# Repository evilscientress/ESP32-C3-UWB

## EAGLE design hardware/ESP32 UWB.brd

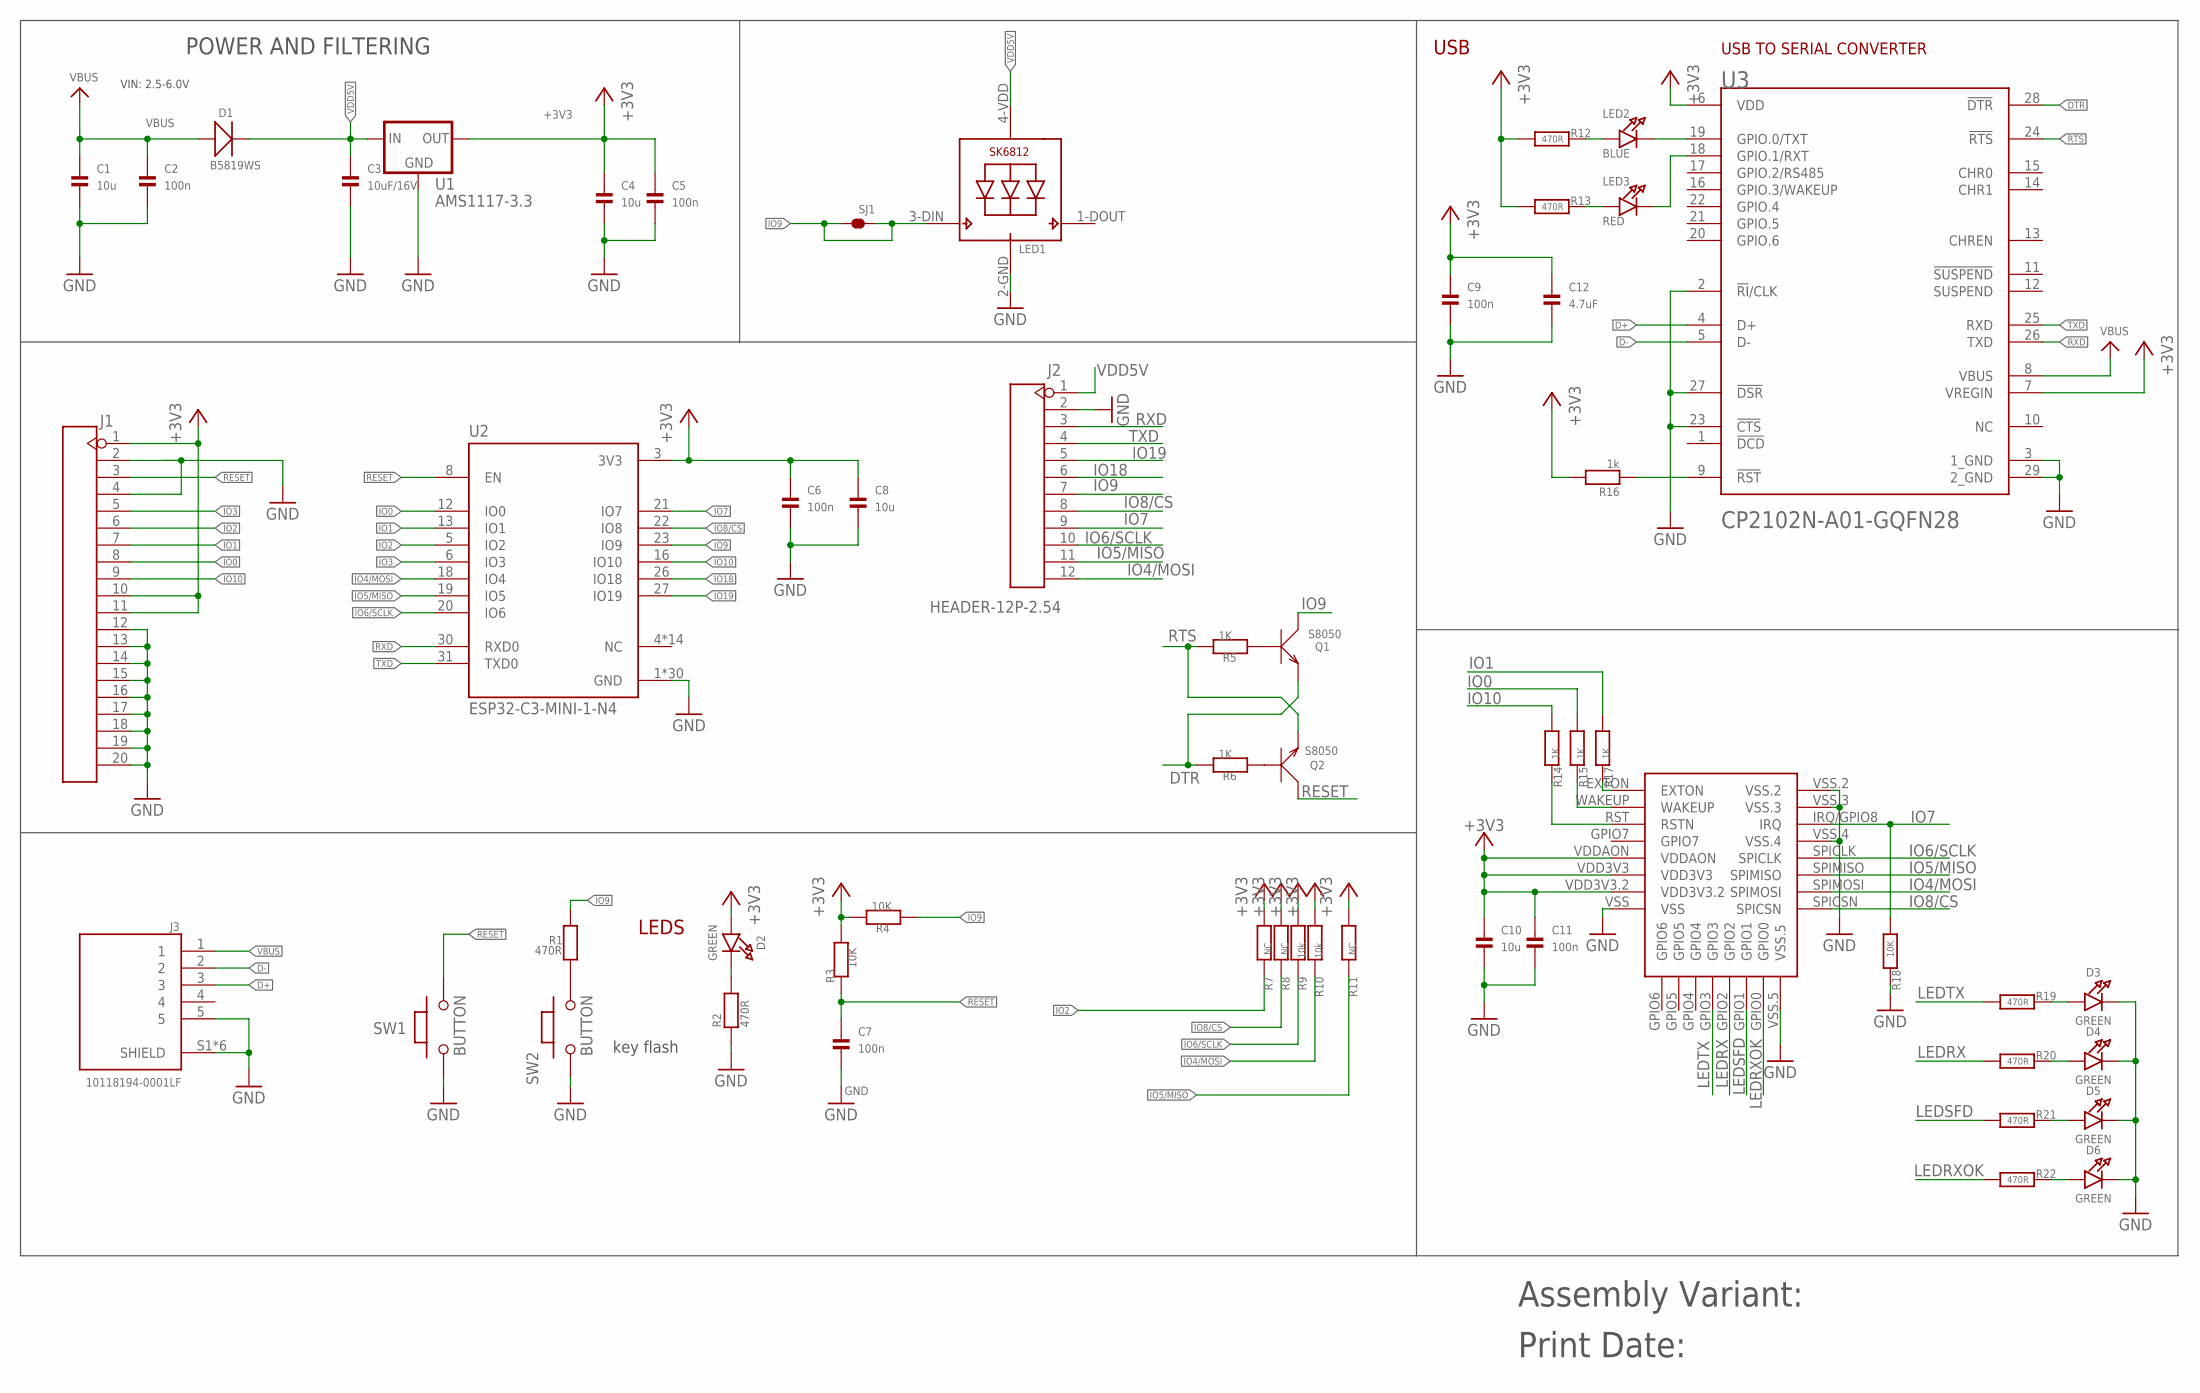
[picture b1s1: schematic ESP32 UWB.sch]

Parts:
C1, C4, C8, C10: 10u; 0603
C2, C5, C6, C7, C9, C11: 100n; 0603
C3: 10uF/16V; 0603
C12: 4.7uF; 0603
D1: B5819WS; SOD323
D2, D3, D4, D5, D6: GREEN; CHIPLED_0805_NOOUTLINE
J1: HEADER-20P-2.54; 20P-2.54
J2: HEADER-12P-2.54; 12P-2.54
J3: 10118194-0001LF; AMPHENOL_10118194-0001LF
LED1: SK6812_3535; LED3535
LED2: BLUE; CHIPLED_0603_NOOUTLINE
LED3: RED; CHIPLED_0603_NOOUTLINE
Q1, Q2: S8050; SOT23
R1, R2, R12, R13, R19, R20, R21, R22: 470R; 0603
R3, R4, R18: 10K; 0603
R5, R6, R14, R15, R17: 1K; 0603
R7, R8, R11: NC; 0603
R9, R10: 10k; 0603
R16: 1k; 0603
SJ1: SJS; SJ_S
SW1, SW2: BUTTON; 157SW
U1: AMS1117-3.3; SOT223
U2: ESP32-C3-MINI-1-N4; XCVR_ESP32-C3-MINI-1-N4
U3: SILICON_LABS_CP2102N-A01-GQFN28SILICON_LABS_CP210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; SILICON_LABS_CP2102N-A01-GQFN28_3
U4: DWM1000

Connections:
+3V3: C4.1, C5.1, C6.1, C8.1, C9.1, C10.1, C11.1, C12.1, D2.A, J1.1, J1.10, J1.11, R3.2, R4.2, R7.1, R8.1, R9.1, R10.1, R11.1, R12.1, R13.1, R16.2, U1.3 (OUT), U2.3 (3V3), U3.6 (VDD), U3.7 (VREGIN), U4.VDD3V3, U4.VDD3V3.2, U4.VDDAON
D+: J3.3, U3.4 (D+)
D-: J3.2, U3.5 (D-)
DTR: Q1.2 (E), R6.2, U3.28 (!DTR!)
GND: C1.2, C2.2, C3.2, C4.2, C5.2, C6.2, C7.2, C8.2, C9.2, C10.2, C11.2, C12.2, D3.C, D4.C, D5.C, D6.C, J1.2, J1.4, J1.12, J1.13, J1.14, J1.15, J1.16, J1.17, J1.18, J1.19, J1.20, J2.2, J3.5, J3.S1 (SHIELD), J3.S2 (SHIELD), J3.S3 (SHIELD), J3.S4 (SHIELD), J3.S5 (SHIELD), J3.S6 (SHIELD), LED1.2-GND (GND), R2.1, R18.2, SW1.1, SW2.1, U1.2 (GND), U2.1 (GND), U2.2 (GND), U2.11 (GND), U2.14 (GND), U2.36 (GND), U2.37 (GND), U2.38 (GND), U2.39 (GND), U2.40 (GND), U2.41 (GND), U2.42 (GND), U2.43 (GND), U2.44 (GND), U2.45 (GND), U2.46 (GND), U2.47 (GND), U2.48 (GND), U2.49_1 (GND), U2.49_2 (GND), U2.49_3 (GND), U2.49_4 (GND), U2.49_5 (GND), U2.49_6 (GND), U2.49_7 (GND), U2.49_8 (GND), U2.49_9 (GND), U2.50 (GND), U2.51 (GND), U2.52 (GND), U2.53 (GND), U3.2 (!RI!/CLK), U3.3 (1_GND), U3.23 (!CTS!), U3.27 (!DSR!), U3.29 (2_GND), U4.VSS, U4.VSS.2, U4.VSS.3, U4.VSS.4, U4.VSS.5
IO0: J1.8, R15.1, U2.12 (IO0)
IO1: J1.7, R17.1, U2.13 (IO1)
IO2: J1.6, R7.2, U2.5 (IO2)
IO3: J1.5, U2.6 (IO3)
IO4/MOSI: J2.12, R10.2, U2.18 (IO4), U4.SPIMOSI
IO5/MISO: J2.11, R11.2, U2.19 (IO5), U4.SPIMISO
IO6/SCLK: J2.10, R9.2, U2.20 (IO6), U4.SPICLK
IO7: J2.9, R18.1, U2.21 (IO7), U4.IRQ/GPIO8 (IRQ)
IO8/CS: J2.8, R8.2, U2.22 (IO8), U4.SPICSN
IO9: J2.7, LED1.3-DIN (DI), Q1.3 (C), R1.2, R4.1, SJ1.1, SJ1.2, U2.23 (IO9)
IO10: J1.9, R14.1, U2.16 (IO10)
IO18: J2.6, U2.26 (IO18)
IO19: J2.5, U2.27 (IO19)
LEDRX: R20.1, U4.GPIO2
LEDRXOK: R22.1, U4.GPIO0
LEDSFD: R21.1, U4.GPIO1
LEDTX: R19.1, U4.GPIO3
unnamed: D3.A, R19.2
unnamed: LED2.A, R12.2
unnamed: LED2.C, U3.19 (GPIO.0/TXT)
unnamed: LED3.A, R13.2
unnamed: D2.C, R2.2
unnamed: LED3.C, U3.18 (GPIO.1/RXT)
unnamed: R16.1, U3.9 (!RST!)
unnamed: R17.2, U4.EXTON
unnamed: R15.2, U4.WAKEUP
unnamed: R14.2, U4.RST (RSTN)
unnamed: Q2.1 (B), R6.1
unnamed: Q1.1 (B), R5.1
unnamed: R1.1, SW2.2
unnamed: D4.A, R20.2
unnamed: D5.A, R21.2
unnamed: D6.A, R22.2
RESET: C7.1, J1.3, Q2.3 (C), R3.1, SW1.2, U2.8 (EN)
RTS: Q2.2 (E), R5.2, U3.24 (!RTS!)
RXD: J2.3, U2.30 (RXD0), U3.26 (TXD)
TXD: J2.4, U2.31 (TXD0), U3.25 (RXD)
VBUS: C1.1, C2.1, D1.+, J3.1, U3.8 (VBUS)
VDD5V: C3.1, D1.-, J2.1, LED1.4-VDD (VDD), U1.1 (IN)

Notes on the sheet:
USB
LEDS
USB TO SERIAL CONVERTER
key flash
POWER AND FILTERING
VIN: 2.5-6.0V
Assembly Variant:
Print Date:

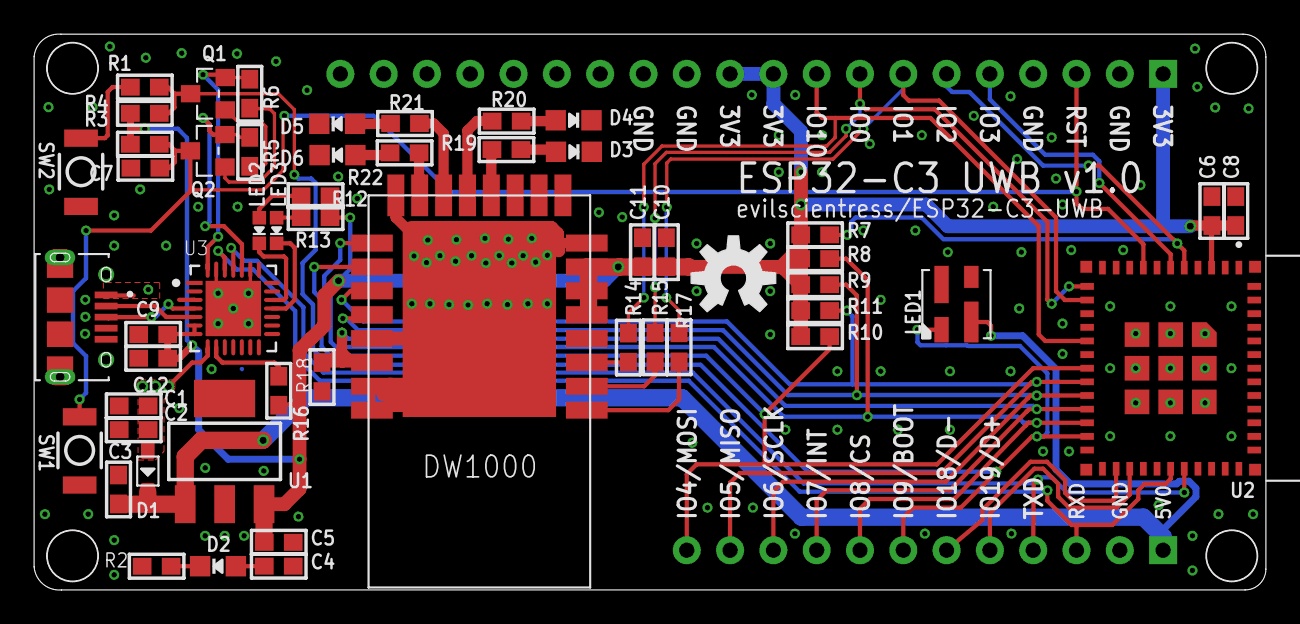
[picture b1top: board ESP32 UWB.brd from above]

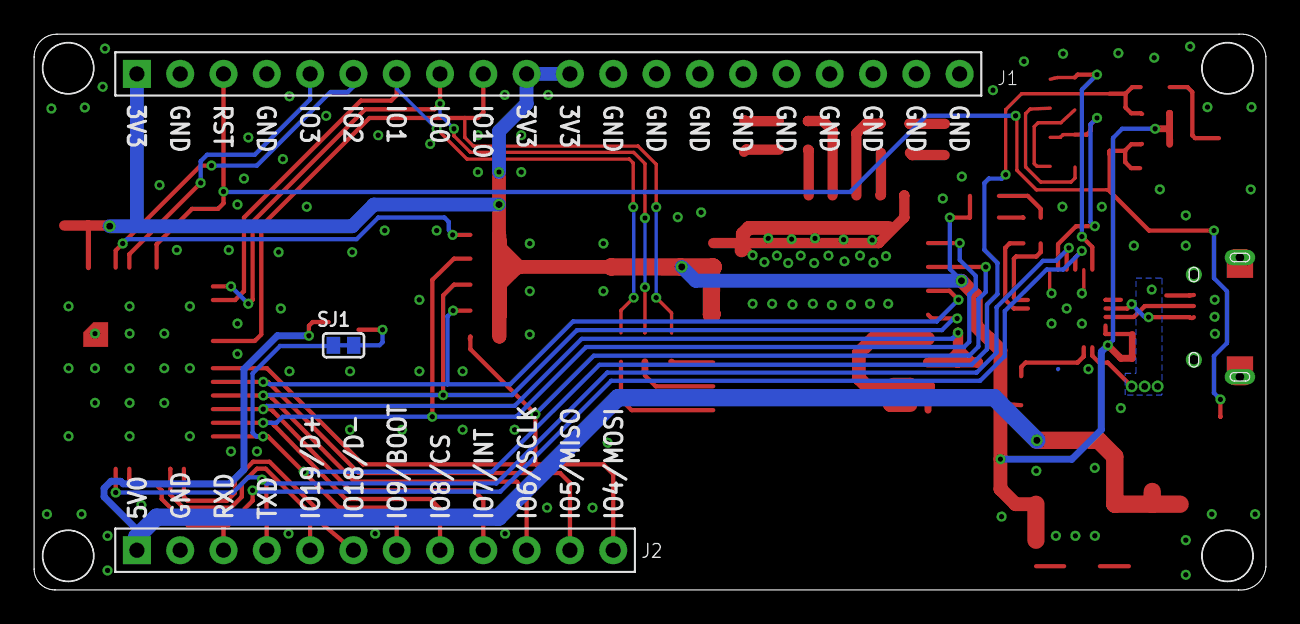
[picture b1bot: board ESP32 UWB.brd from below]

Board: 2 copper layers, 72.3 x 32.6 mm, 56 parts (3 on the bottom side), 44 nets.

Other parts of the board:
U$1: OSHW-LOGO-M

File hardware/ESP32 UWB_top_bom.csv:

Comment,Designator,Footprint,LCSC Part #
1K,R5 R6 R14 R15 R16 R17,0603,C21190
10K,R3 R4 R7 R8 R9 R10 R11 R18,0603,C25804
470R,R1 R2 R12 R13 R19 R20 R21 R22,0603,C23179
4.7uF,C12,0603,C19666
10uF/25V,C1 C3 C4 C8 C10,0603,C96446
100n,C2 C5 C6 C7 C9 C11,0603,C14663
10118194-0001LF,J3,AMPHENOL_10118194-0001LF,C132563
AMS1117-3.3,U1,SOT223,C6186
Schottky Diode 40V 1A 600MV,D1,SOD323,C191023
Pushbutton SMD 3×4×2.5mm,SW1 SW2,157SW,C843669
BU01 UWB RF Module,U4,DWM1000,C503604
ESP32-C3-MINI-1-N4,U2,XCVR_ESP32-C3-MINI-1-N4,C2838502
LED 0603 red,"LED2, LED3",0603,C2286
LED 0805 blue,D2,0805,C2293
LED 0805 yellow,D3 D4 D5 D6,0805,C2296
S8050,Q1 Q2,SOT23,C2146
CP2102N or CP2102/9 USB Serial Converter,U3,GQFN-28,C6568

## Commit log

2022-01-05 swaped ESP module to ESP32-C3-MINI
2022-01-05 schematic cleanup and pdf export
2022-01-05 added gitignore file
2022-01-05 renamed pcb files, updated gerber package
2022-01-06 switched various parts to more newer or more available part, moved all to the front
    Switched Parts:
    * USB-Serial Converter CP2104 -> CP2102N
    * 3.3V LDO
    * Micro USB Connector
    All parts are now on the front side which means expensive double sided assembly is no longer needed.
2022-01-06 switched resistor and capacitor footprints, placed labels
2022-01-06 Added WS2812b led for status display
2022-01-06 fixed floating input pins
2022-01-06 added solder jumper for optionally disabling the ws2812 led
2022-01-06 updated gerber files and schematic pdf
2022-01-06 added images of top and bottom of the pcb
2022-01-07 Updated SJ Package to my own (smaller) version
2022-01-07 fixed device prefixes, removed duplicate supply symbols
2022-01-07 renumbered parts
2022-01-07 replaced footprint of C7
2022-01-07 updated library
2022-01-07 replaced WS2812 with SK6812-mini-e
2022-01-07 added production files (gerber, bom, cpl) for latest version
2022-01-09 fixed schematic pdf
2022-01-09 added assembly variant without USB serial converter
2022-01-09 add version converted to KiCad
2022-01-15 update schematic to use built-in kicad symbols
2022-01-15 change all footprints in schematic
2022-01-15 fox pcb
2022-01-15 tweak pcb and fix all DRC errors
2022-01-15 first silkscreen tweaks
2022-01-15 more tweaks
2022-01-15 tweak silkscreen and 3d model
2022-01-15 tweak silkscreen orientation and more
2022-01-15 swap pushbuttons
2022-01-15 clean up schematic
2022-01-15 add keepout zone and labels for LEDs
2022-01-15 make DRC happy
2022-01-15 remove cache
2022-01-15 add kicad gitignore
2022-01-15 remove unused symbols and footprints
2022-01-16 further cleanup and improvment of the KiCad version of the PCB
2022-01-16 label buttons
2022-01-16 add JLCJLCJLCJLC
2022-01-16 adjust silkscreen
2022-01-16 add BOM fields and tweak symbols and parts
2022-01-16 tweak bom some more
2022-01-16 add files for JLCPCB
2022-01-16 more fabrication files

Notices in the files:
parts and their libraries:
microbuilder: This work is placed in the public domain, and may be freely used for commercial and non-commercial work with the following conditions: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
SparkFun-PowerIC: Licensing: Creative Commons ShareAlike 4.0 International - https://creativecommons.org/licenses/by-sa/4.0
